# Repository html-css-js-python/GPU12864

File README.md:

# VidiaG Force RT-X12864

<p align="center">

</p>

VidiaG Force RT-X12864 is an open-source, microcontroller-based GPU designed for 128x64 GLCD displays. It acts as a dedicated graphics processing unit, handling framebuffer management, rendering, and communication with the display independently from the main CPU.

Unlike a typical GLCD library, the CPU does not directly control the display. Instead, it sends high-level drawing commands to the RT-X12864 GPU, which performs all rendering operations and updates the GLCD using its own framebuffer.

## Features

* Dedicated GPU architecture for 128x64 GLCD displays
* Independent framebuffer management
* I&sup2;C communication between CPU and GPU
* Text rendering with 5x7 and 8x8 fonts
* Pixel, line, rectangle, and filled rectangle drawing
* Circle and filled circle rendering
* Bitmap rendering from PROGMEM
* Open-source hardware and software
* Expandable command-based communication protocol

## Architecture

```
CPU (Master)
    |
    | I²C Commands (400 kHz)
    v
VidiaG Force RT-X12864 GPU
    |
    | Framebuffer Rendering
    v
CustomGLCD Driver
    |
    v
128x64 GLCD Display
```

> [!IMPORTANT]
> The CPU only sends high-level commands such as drawing pixels, lines, text, and bitmaps. The GPU handles all low-level rendering and display communication.

## Hardware

| Component         | Description                                                |
| ----------------- | ---------------------------------------------------------- |
| GPU               | Arduino Uno R4 WiFi                                        |
| CPU               | Any compatible I2C master (tested with Arduino Nano Every) |
| Display           | AG12864AHF / KS0108-compatible 128x64 GLCD                 |
| Interface         | I&sup2;C Fast-Mode (400 kHz)                               |
| VRAM              | 1 KB framebuffer                                           |
| Power Consumption | Approximately 255 mA including the display (idle)          |

## Installation

1. Upload `gpu_soft/ScreenI2C/ScreenI2C.ino` to the Arduino Uno R4 WiFi.
2. Connect the GLCD display to the GPU according to the schematic.
3. Connect the CPU board to the GPU via I&sup2;C using `GND`, `VCC`, `SCL`, and `SDA`.
4. Include `GPU12864.h` in your CPU project.
5. Call `gpuBegin()` before using any GPU functions.

## Basic Usage

```cpp
#include "GPU12864.h"

void setup()
{
    gpuBegin();
    gpuClear();

    gpuDrawText(1, 1, "Hello, World!", FONT_5X7);
    gpuDrawLine(0, 0, 127, 63);

    gpuUpdate();
}

void loop()
{
}
```

## Available Commands

The API is function-based rather than object-oriented.

> Functions, yes, functions. **Because yes**.
>
> It was simpler to implement this way. :P

| Command                                                                                     | Function                                                     |
| ------------------------------------------------------------------------------------------- | ------------------------------------------------------------ |
| `gpuBegin()`                                                                                | Begins communication between CPU and GPU (takes about 1.2 s) |
| `gpuClear()`                                                                                | Clear the framebuffer                                        |
| `gpuUpdate()`                                                                               | Send the framebuffer to the GLCD                             |
| `gpuDrawPixel(uint8_t x, uint8_t y, bool color = true)`                                     | Draw a single pixel                                          |
| `gpuDrawLine(uint8_t x0, uint8_t y0, uint8_t x1, uint8_t y1, bool color = true)`            | Draw a line                                                  |
| `gpuDrawRect(uint8_t x, uint8_t y, uint8_t w, uint8_t h, bool color = true)`                | Draw a rectangle                                             |
| `gpuFillRect(uint8_t x, uint8_t y, uint8_t w, uint8_t h, bool color = true)`                | Draw a filled rectangle                                      |
| `gpuDrawCircle(uint8_t x, uint8_t y, uint8_t r, bool color = true)`                         | Draw a circle                                                |
| `gpuFillCircle(uint8_t x, uint8_t y, uint8_t r, bool color = true)`                         | Draw a filled circle                                         |
| `gpuDrawText(uint8_t x, uint8_t y, const char* text, uint8_t fontId, bool color = true)`    | Render text                                                  |
| `gpuDrawBitmap(uint8_t x, uint8_t y, const uint8_t *bitmap, uint8_t width, uint8_t height)` | Render a bitmap stored in `PROGMEM`                          |

> [!TIP]
> You can use `gpuFillRect()` instead of `gpuClear()` when you want to clear only part of the screen to avoid screen flashing on refresh.

## Demos

The repository includes several demonstration programs:

* Hello World
* Font rendering demo
* Shapes and primitives demo
* Sine wave graph
* Live scrolling graph
* Bouncing ball animation
* Rotating 3D cube
* Benchmark demo
* Full demonstration sequence

## PCB

The repository includes the complete KiCad project and manufacturing files for the RT-X12864 adapter PCB, including:

* `.kicad_pro` project file
* `.kicad_sch` schematic
* `.kicad_pcb` PCB layout
* Gerber files (`.gbr`)
* Drill files (`.drl`)
* `gerber.zip` ready for PCB fabrication

## Documentation

* [Technical Specification](docs/specs.md)
* [Bitmap Conversion and Rendering](docs/bitmap.md)
* [I&sup2;C Communication Protocol](docs/protocol.md)
* [Additional Drivers](docs/additional_drivers.md)
* [Fun Specifications (Easter Egg)](/fun_specs.md)

## Hardware Files
* [Project Files](/hardware/GPU12864)
* [Gerber Files](/hardware/GPU12864/gerber)
* [Gerber Package](/hardware/GPU12864/gerber.zip)

> [!NOTE]
> This is not an RTX graphics card. It is a custom, microcontroller-based 2D GPU for GLCD displays.

This project is released as open-source hardware and software. You are free to study, modify, and distribute it under the terms of the [license](/LICENSE).

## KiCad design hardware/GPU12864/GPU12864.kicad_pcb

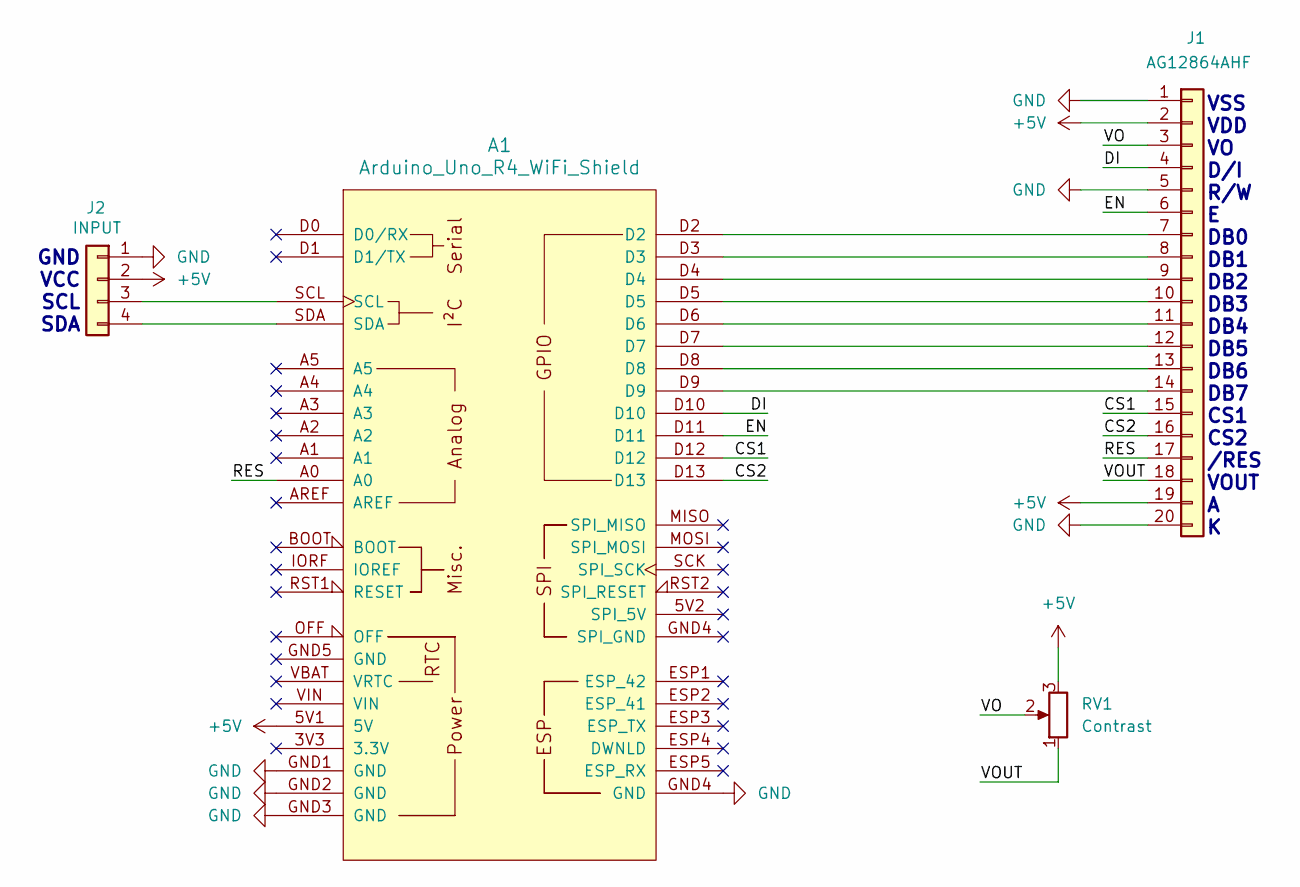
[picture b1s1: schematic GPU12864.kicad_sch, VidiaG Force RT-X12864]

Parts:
A1: Arduino_Uno_R4_WiFi_Shield
J1: AG12864AHF; PinHeader_1x20_P2.54mm_Vertical
J2: INPUT; PinHeader_1x04_P2.54mm_Vertical
RV1: Contrast; Potentiometer_Runtron_RM-065_Vertical

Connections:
+5V: A1.5V1 (5V), J1.2, J1.19, J2.2, RV1.3
/CS1: A1.D12, J1.15
/CS2: A1.D13, J1.16
/DI: A1.D10, J1.4
/EN: A1.D11, J1.6
/RES: A1.A0, J1.17
/VO: J1.3, RV1.2
/VOUT: J1.18, RV1.1
GND: A1.GND1 (GND), A1.GND2 (GND), A1.GND3 (GND), A1.GND4 (GND), J1.1, J1.5, J1.20, J2.1
unnamed: A1.D2, J1.7
unnamed: A1.D3, J1.8
unnamed: A1.D4, J1.9
unnamed: A1.D5, J1.10
unnamed: A1.D6, J1.11
unnamed: A1.D7, J1.12
unnamed: A1.D8, J1.13
unnamed: A1.D9, J1.14
unnamed: A1.SCL, J2.3
unnamed: A1.SDA, J2.4

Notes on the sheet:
VSS VDD VO D/I R/W E DB0 DB1 DB2 DB3 DB4 DB5 DB6 DB7 CS1 CS2 /RES VOUT A K
GND VCC SCL SDA

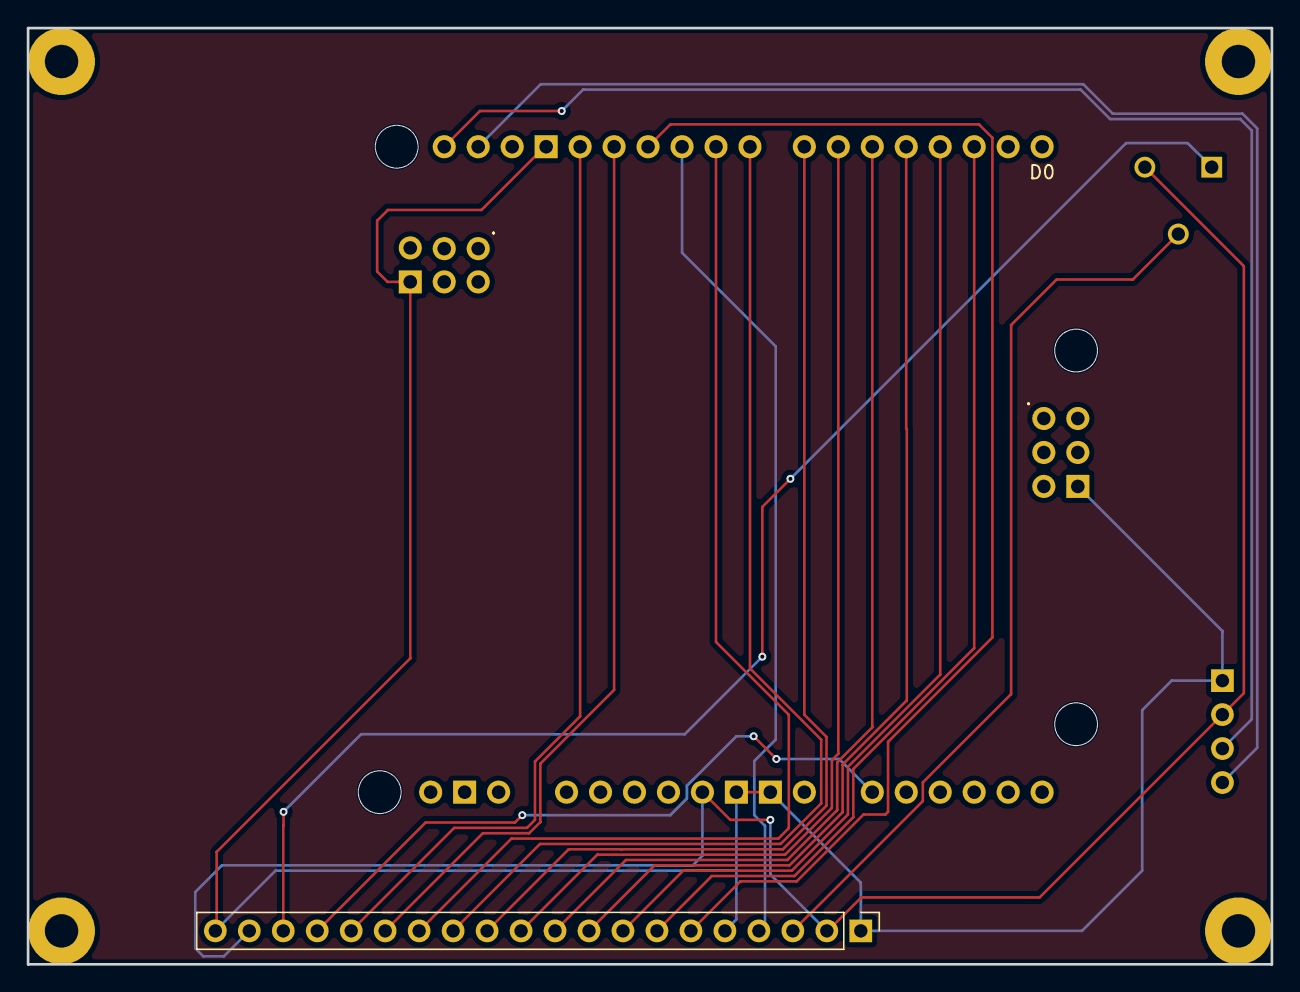
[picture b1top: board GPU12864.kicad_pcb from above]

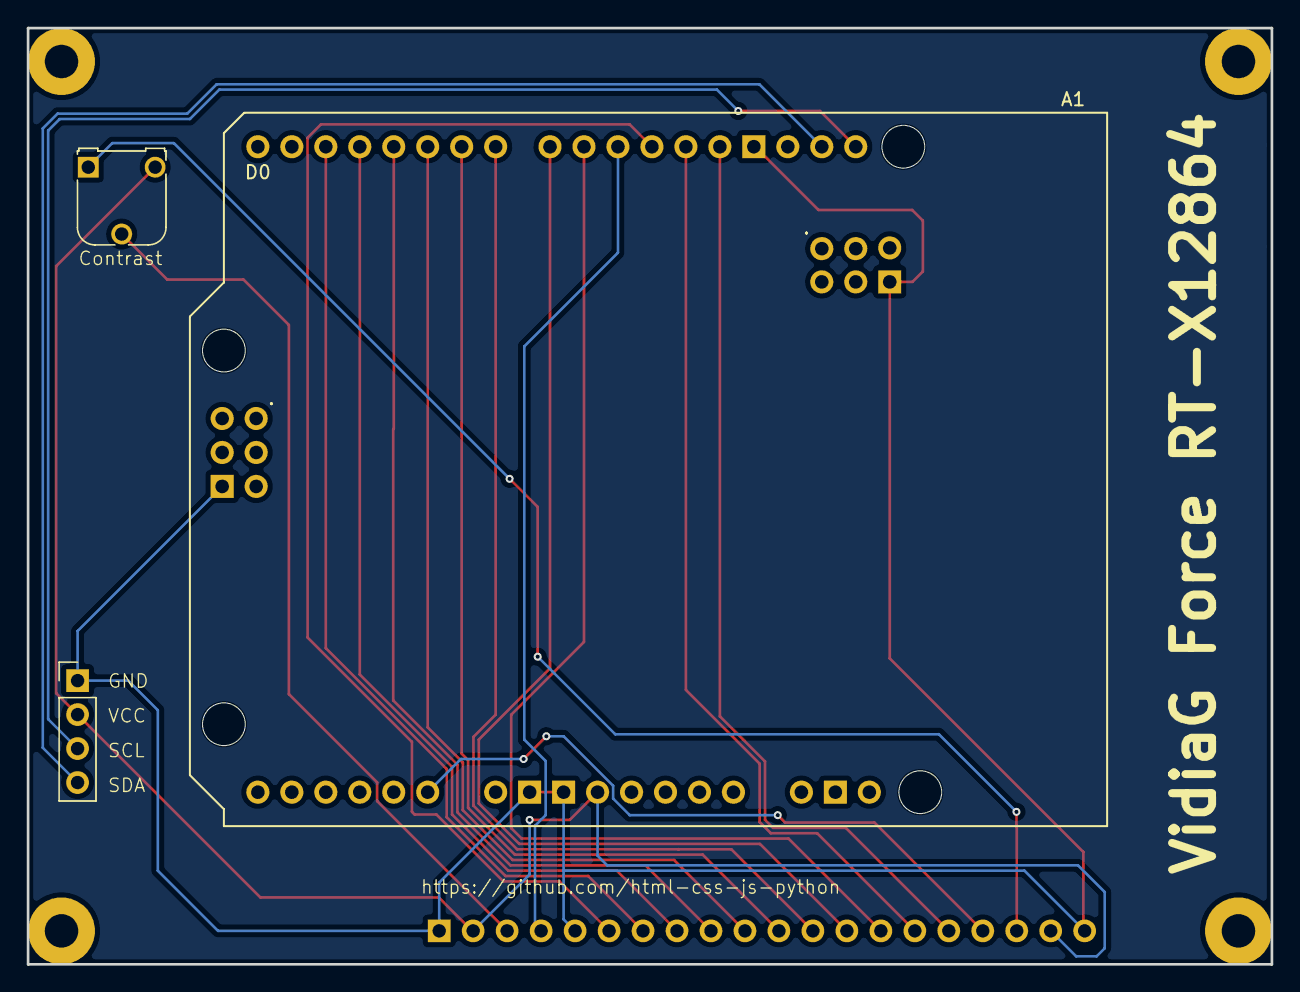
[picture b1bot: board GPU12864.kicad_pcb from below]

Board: 2 copper layers, 93.0 x 70.0 mm, 4 parts (2 on the bottom side), 19 nets.
